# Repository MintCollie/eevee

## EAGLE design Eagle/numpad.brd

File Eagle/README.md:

# eevee
eevee - the eevee inspired macro keyboard.

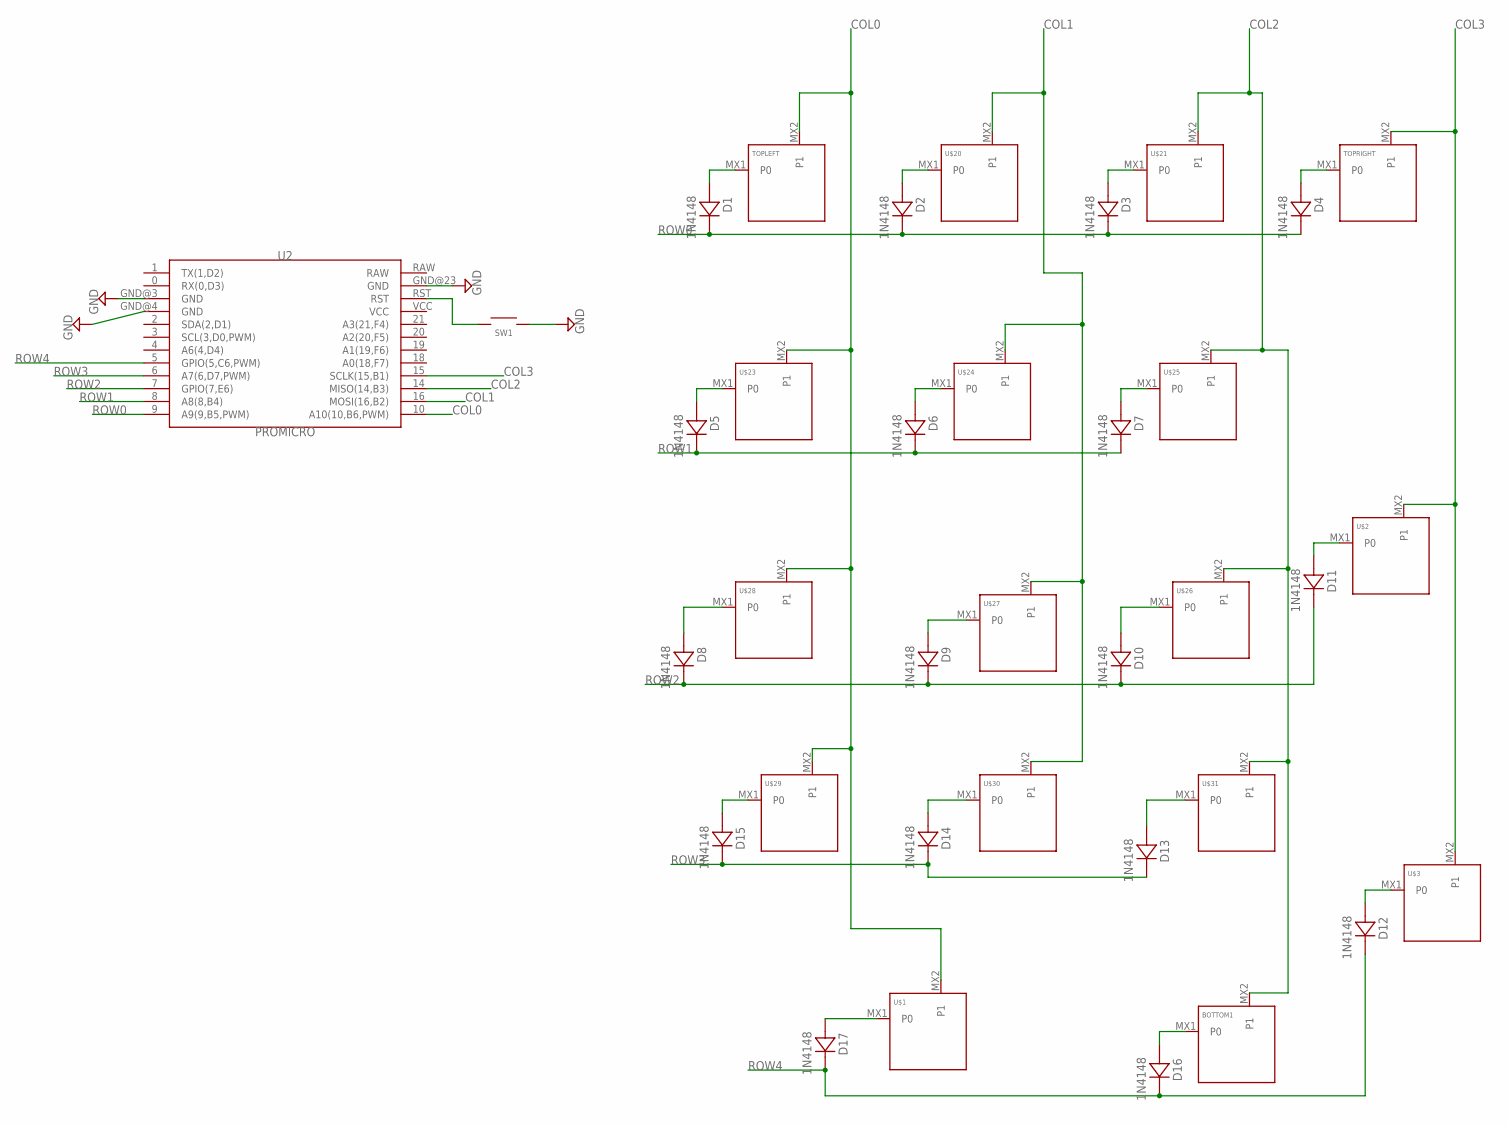
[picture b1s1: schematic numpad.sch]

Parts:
BOTTOM1: KEYSWITCH-PLAIN-MX-1U; MX-1U
D1, D2, D3, D4, D5, D6, D7, D8, D9, D10, D11, D12, D13, D14, D15, D16, D17: 1N4148; DO-35
SW1: SWITCH-SMD-SCHURTER-1241.1612.11
TOPLEFT: KEYSWITCH-PLAIN-MX-1U; MX-1U
TOPRIGHT: KEYSWITCH-PLAIN-MX-1U; MX-1U
U2: PROMICRO
U$1: KEYSWITCH-PLAIN-MX-2U-FLIPPED; MX-2U-FLIPPED
U$2, U$3: KEYSWITCH-PLAIN-MX-2U-ROTATED; MX-2U-ROTATED
U$20, U$21, U$23, U$24, U$25, U$26, U$27, U$28, U$29, U$30, U$31: KEYSWITCH-PLAIN-MX-1U; MX-1U

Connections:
COL0: TOPLEFT.MX2 (P1), U2.10 (A10(10,B6,PWM)), U$1.MX2 (P1), U$23.MX2 (P1), U$28.MX2 (P1), U$29.MX2 (P1)
COL1: U2.16 (MOSI(16,B2)), U$20.MX2 (P1), U$24.MX2 (P1), U$27.MX2 (P1), U$30.MX2 (P1)
COL2: BOTTOM1.MX2 (P1), U2.14 (MISO(14,B3)), U$21.MX2 (P1), U$25.MX2 (P1), U$26.MX2 (P1), U$31.MX2 (P1)
COL3: TOPRIGHT.MX2 (P1), U2.15 (SCLK(15,B1)), U$2.MX2 (P1), U$3.MX2 (P1)
GND: SW1.2A (2), SW1.2B (2), U2.GND@3 (GND), U2.GND@4 (GND), U2.GND@23 (GND)
unnamed: SW1.1A (1), SW1.1B (1), U2.RST
unnamed: D1.A, TOPLEFT.MX1 (P0)
unnamed: D2.A, U$20.MX1 (P0)
unnamed: D3.A, U$21.MX1 (P0)
unnamed: D4.A, TOPRIGHT.MX1 (P0)
unnamed: D15.A, U$29.MX1 (P0)
unnamed: D5.A, U$23.MX1 (P0)
unnamed: D6.A, U$24.MX1 (P0)
unnamed: D7.A, U$25.MX1 (P0)
unnamed: D11.A, U$2.MX1 (P0)
unnamed: D10.A, U$26.MX1 (P0)
unnamed: D9.A, U$27.MX1 (P0)
unnamed: D8.A, U$28.MX1 (P0)
unnamed: D14.A, U$30.MX1 (P0)
unnamed: D13.A, U$31.MX1 (P0)
unnamed: BOTTOM1.MX1 (P0), D16.A
unnamed: D17.A, U$1.MX1 (P0)
unnamed: D12.A, U$3.MX1 (P0)
ROW0: D1.C, D2.C, D3.C, D4.C, U2.9 (A9(9,B5,PWM))
ROW1: D5.C, D6.C, D7.C, U2.8 (A8(8,B4))
ROW2: D8.C, D9.C, D10.C, D11.C, U2.7 (GPIO(7,E6))
ROW3: D13.C, D14.C, D15.C, U2.6 (A7(6,D7,PWM))
ROW4: D12.C, D16.C, D17.C, U2.5 (GPIO(5,C6,PWM))

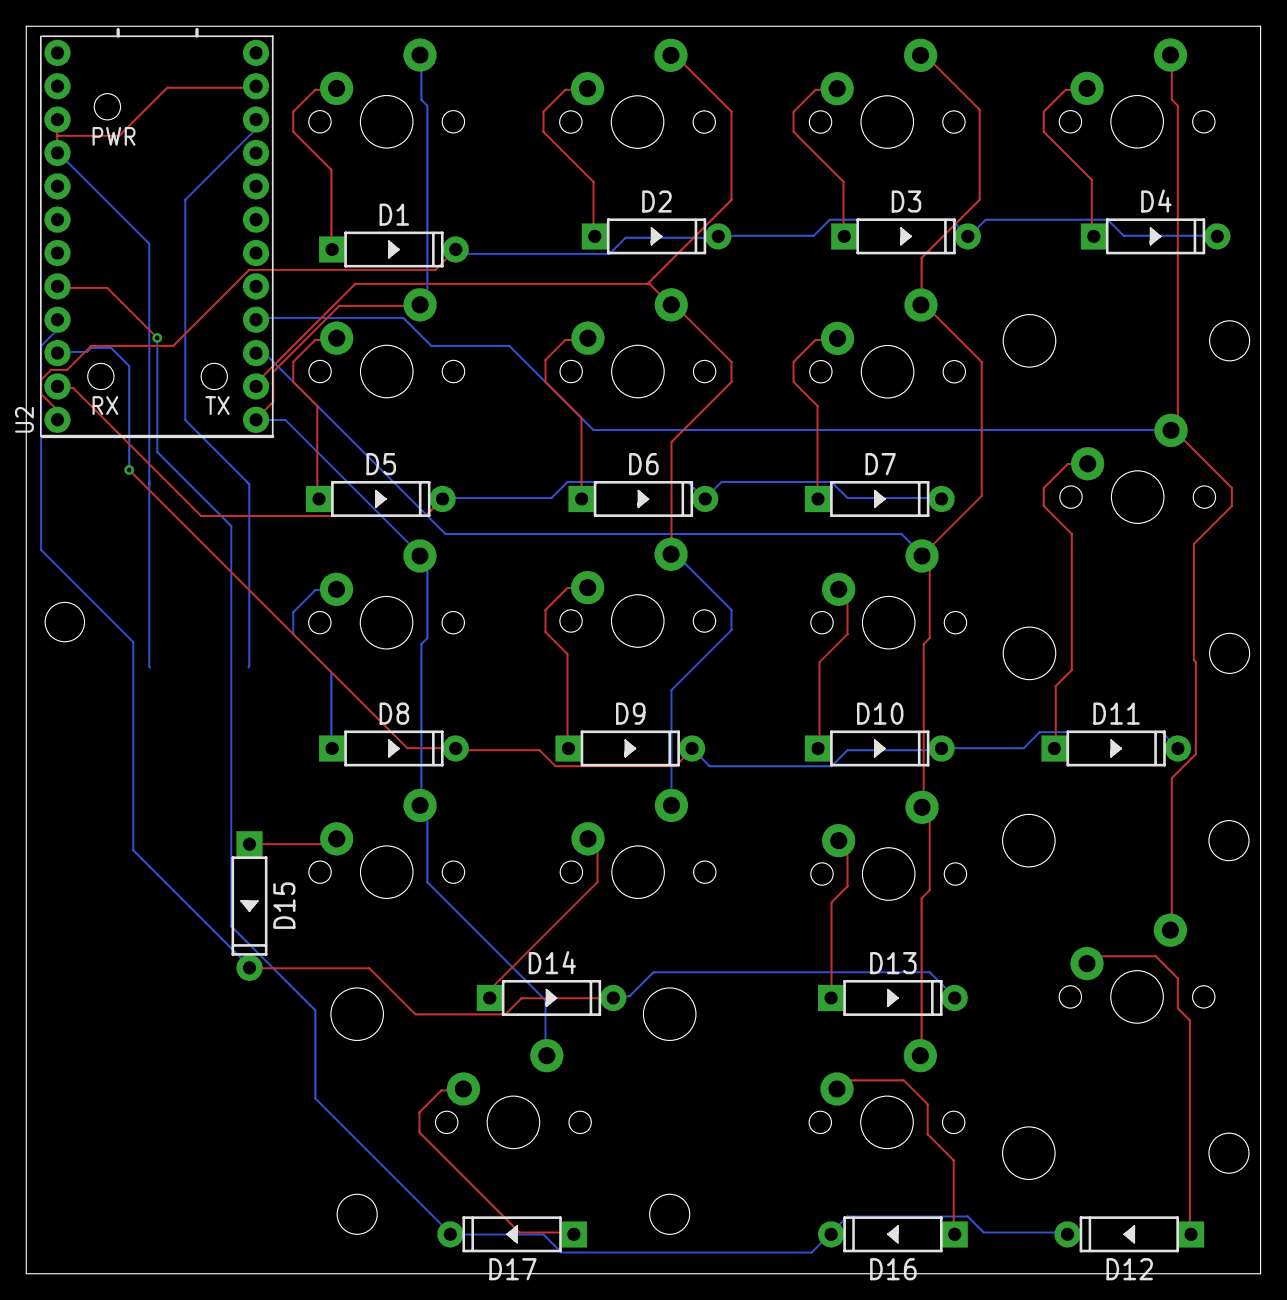
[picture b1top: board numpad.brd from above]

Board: 2 copper layers, 94.0 x 95.0 mm, 36 parts (1 on the bottom side), 28 nets.

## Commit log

2020-05-02 added first schematic
2020-05-06 added switches and dxf of layout
2020-05-06 created folder for files and moved them to it
2020-05-06 moved readme
2020-05-06 needed to replace switches. added diodes.
2020-05-06 moved files due to eagle error
2020-05-06 finished first test of board, need to finish placement of switches
2020-05-06 deleted old testing folder
2020-05-06 moved license back to correct area
2020-05-07 added hole
2020-05-08 replaced promicro and relayed wire
2020-05-08 cleaning up working dir
2020-06-26 created gerber for test prod
